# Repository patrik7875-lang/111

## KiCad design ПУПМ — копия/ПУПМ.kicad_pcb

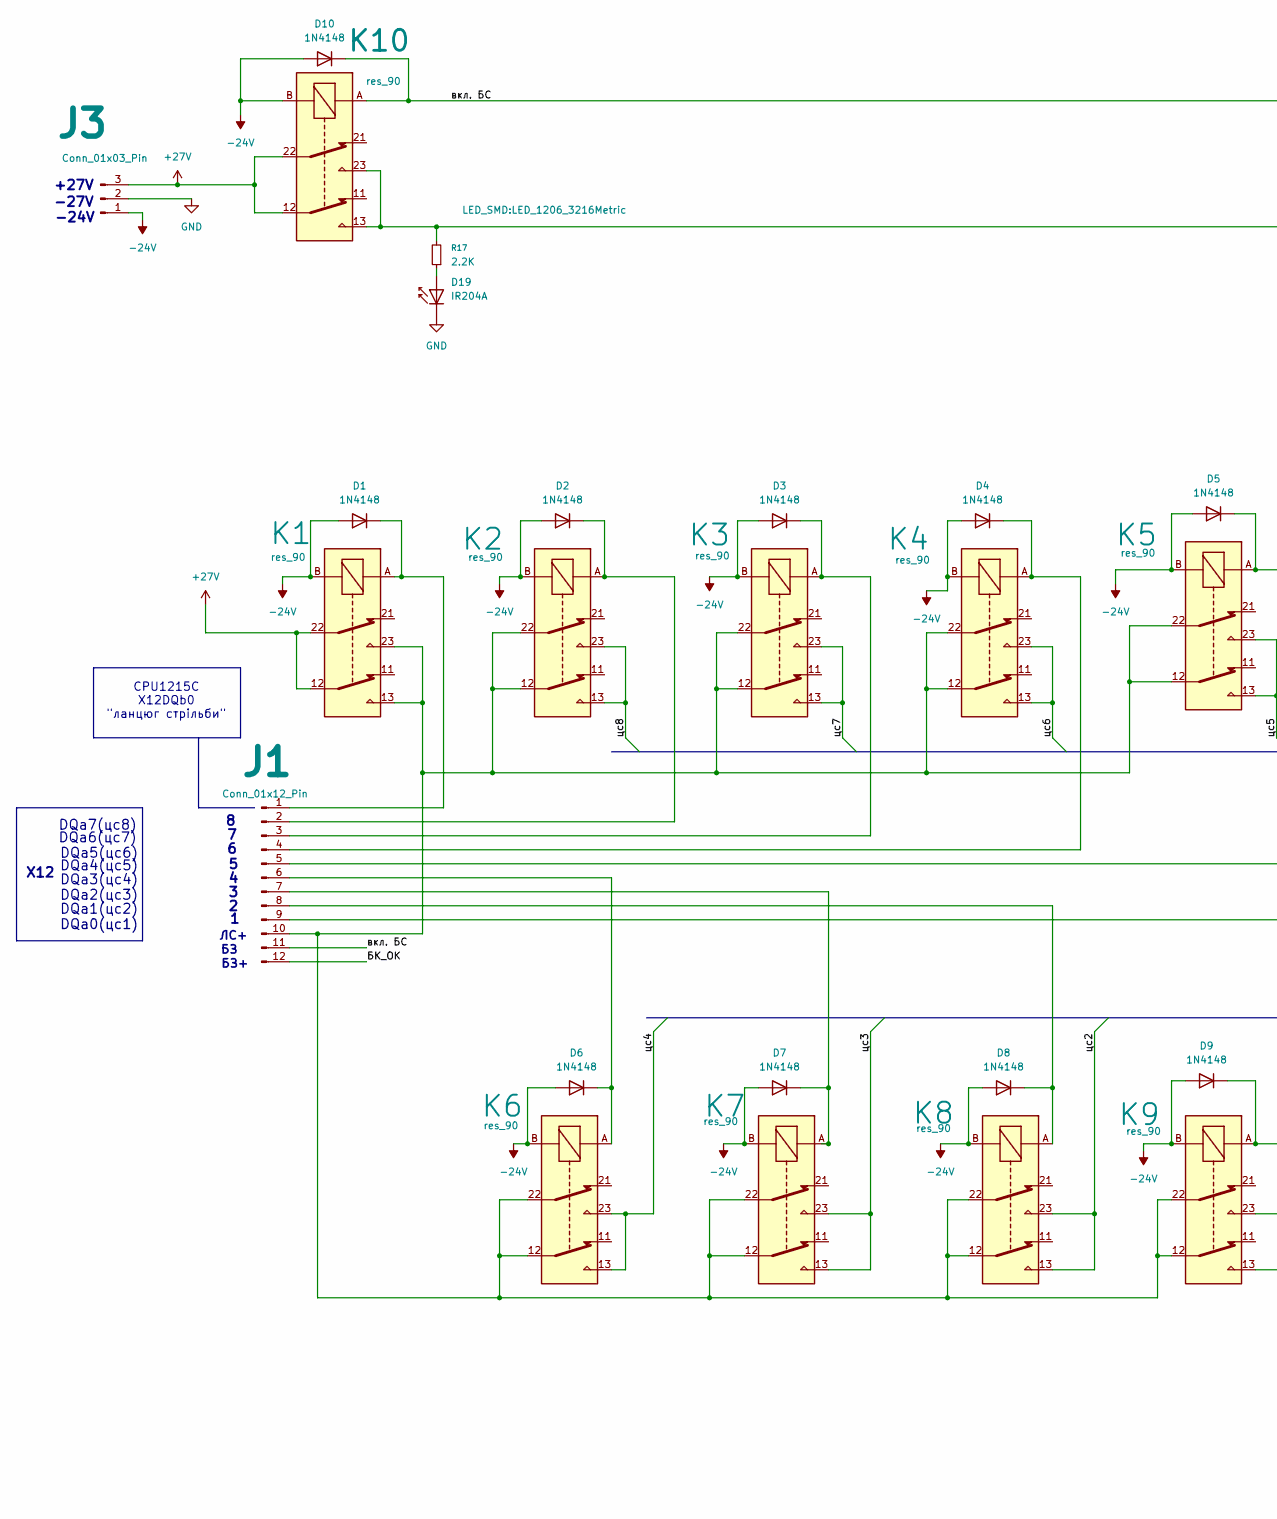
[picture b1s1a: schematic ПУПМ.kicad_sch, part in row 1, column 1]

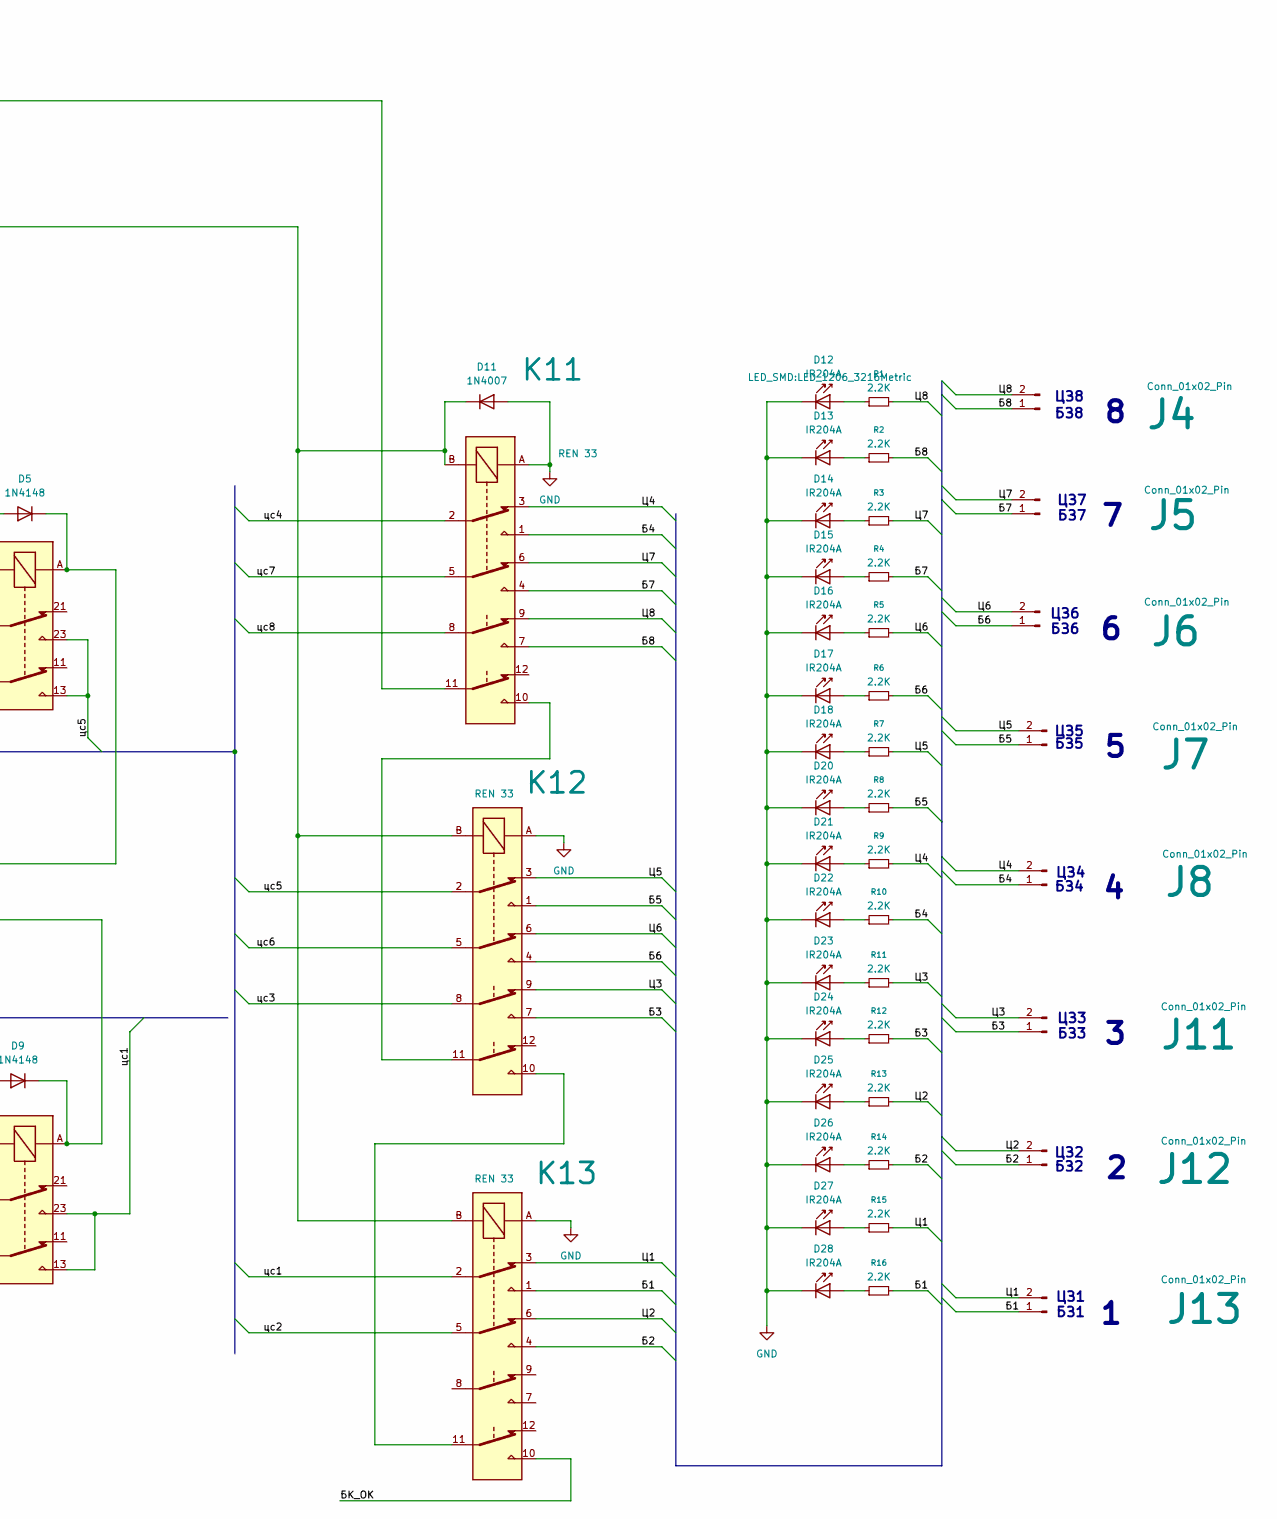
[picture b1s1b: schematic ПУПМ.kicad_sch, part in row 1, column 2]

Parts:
D1, D2, D3, D4, D5, D6, D7, D8, D9, D10: 1N4148; D_SOD-123
D11: 1N4007; D_DO-41_SOD81_P10.16mm_Horizontal
D12, D13, D14, D15, D16, D17, D18, D19, D20, D21, D22, D23, D24, D25, D26, D27, D28: IR204A; LED_1206_3216Metric
J1: Conn_01x12_Pin; TerminalBlock_Phoenix_PT-1,5-12-5.0-H_1x12_P5.00mm_Horizont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
J3: Conn_01x03_Pin; TerminalBlock_MetzConnect_Type701_RT11L03HGLU_1x03_P6.35mm_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
J4, J5, J6, J7, J8, J11, J12, J13: Conn_01x02_Pin; TerminalBlock_MetzConnect_Type701_RT11L02HGLU_1x02_P6.35mm_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
K1, K2, K3, K4, K5, K6, K7, K8, K9, K10: res_90; res90
K11, K12, K13: REN 33
R1, R2, R3, R4, R5, R6, R7, R8, R9, R10, R11, R12, R13, R14, R15, R16, R17: 2.2K; R_1206_3216Metric

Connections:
+27V: J3.3, K1.12, K1.22, K10.12, K10.22
-24V: D1.2 (A), D2.2 (A), D3.2 (A), D4.2 (A), D5.2 (A), D6.2 (A), D7.2 (A), D8.2 (A), D9.2 (A), D10.2 (A), J3.1, K1.B, K2.B, K3.B, K4.B, K5.B, K6.B, K7.B, K8.B, K9.B, K10.B
/Б1: J13.1, K13.1, R16.2
/Б2: J12.1, K13.4, R14.2
/Б3: J11.1, K12.7, R12.2
/Б4: J8.1, K11.1, R10.2
/Б5: J7.1, K12.1, R8.2
/Б6: J6.1, K12.4, R6.2
/Б7: J5.1, K11.4, R4.2
/Б8: J4.1, K11.7, R2.2
/БК_ОК: J1.12, K13.10
/Ц1: J13.2, K13.3, R15.2
/Ц2: J12.2, K13.6, R13.2
/Ц3: J11.2, K12.9, R11.2
/Ц4: J8.2, K11.3, R9.2
/Ц5: J7.2, K12.3, R7.2
/Ц6: J6.2, K12.6, R5.2
/Ц7: J5.2, K11.6, R3.2
/Ц8: J4.2, K11.9, R1.2
/вкл. БС: D10.1 (K), J1.11, K10.A, K11.11
/цс1: K9.13, K9.23, K13.2
/цс2: K8.13, K8.23, K13.5
/цс3: K7.13, K7.23, K12.8
/цс4: K6.13, K6.23, K11.2
/цс5: K5.13, K5.23, K12.2
/цс6: K4.13, K4.23, K12.5
/цс7: K3.13, K3.23, K11.5
/цс8: K2.13, K2.23, K11.8
GND: D11.2 (A), D12.1 (K), D13.1 (K), D14.1 (K), D15.1 (K), D16.1 (K), D17.1 (K), D18.1 (K), D19.1 (K), D20.1 (K), D21.1 (K), D22.1 (K), D23.1 (K), D24.1 (K), D25.1 (K), D26.1 (K), D27.1 (K), D28.1 (K), J3.2, K11.A, K12.A, K13.A
unnamed: D1.1 (K), J1.1, K1.A
unnamed: D2.1 (K), J1.2, K2.A
unnamed: D3.1 (K), J1.3, K3.A
unnamed: D4.1 (K), J1.4, K4.A
unnamed: D5.1 (K), J1.5, K5.A
unnamed: D6.1 (K), J1.6, K6.A
unnamed: D7.1 (K), J1.7, K7.A
unnamed: D8.1 (K), J1.8, K8.A
unnamed: D9.1 (K), J1.9, K9.A
unnamed: D11.1 (K), K10.13, K10.23, K11.B, K12.B, K13.B, R17.2
unnamed: D12.2 (A), R1.1
unnamed: D13.2 (A), R2.1
unnamed: D14.2 (A), R3.1
unnamed: D15.2 (A), R4.1
unnamed: D16.2 (A), R5.1
unnamed: D17.2 (A), R6.1
unnamed: D18.2 (A), R7.1
unnamed: D19.2 (A), R17.1
unnamed: D20.2 (A), R8.1
unnamed: D21.2 (A), R9.1
unnamed: D22.2 (A), R10.1
unnamed: D23.2 (A), R11.1
unnamed: D24.2 (A), R12.1
unnamed: D25.2 (A), R13.1
unnamed: D26.2 (A), R14.1
unnamed: D27.2 (A), R15.1
unnamed: D28.2 (A), R16.1
unnamed: J1.10, K1.13, K1.23, K2.12, K2.22, K3.12, K3.22, K4.12, K4.22, K5.12, K5.22, K6.12, K6.22, K7.12, K7.22, K8.12, K8.22, K9.12, K9.22
unnamed: K11.10, K12.11
unnamed: K12.10, K13.11

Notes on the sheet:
БЗ2
X12
ЦЗ7
DQa1(цс2)
ЦЗ5
БЗ5
ЦЗ1
ЦЗ2
ЛС+
ЦЗ8
DQa7(цс8)
ЦЗ4
DQa5(цс6)
DQa6(цс7)
БЗ3
DQa2(цс3)
DQa4(цс5)
БЗ1
DQa0(цс1)
ЦЗ6
-27V
-24V
БЗ+
CPU1215C X12DQb0 "ланцюг стрільби"
DQa3(цс4)
БЗ4
+27V
БЗ6
БЗ8
БЗ7
ЦЗ3

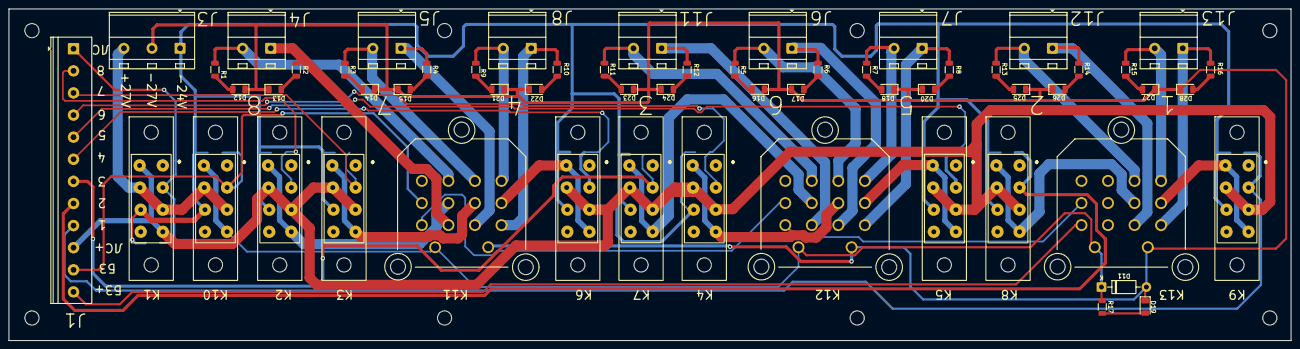
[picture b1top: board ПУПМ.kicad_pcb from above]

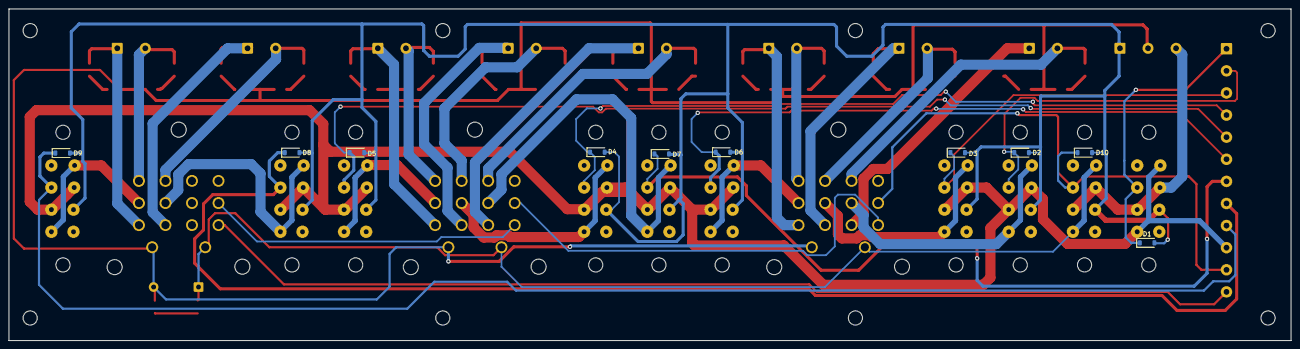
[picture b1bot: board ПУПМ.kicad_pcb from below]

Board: 2 copper layers, 290.0 x 75.0 mm, 68 parts (10 on the bottom side), 59 nets.
